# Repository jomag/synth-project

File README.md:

Project files for an experimental, DIY modular synth in Eurorack format.

## Casing

Threaded strips: 2x5x432 mm (also available in 203.2 mm). Hole distance: 5.08 mm.

https://gie-tec.de/product/threaded-strips/?lang=en

## References

A lot of generic and module specific design tips:
http://dintree.com/

Precision tuning of the AS3340 VCO
https://cabintechglobal.com/tune3340
http://www.alfarzpp.lv/eng/sc/Tuning%20the%20AS3340.pdf

CEM3340 VCO (Voltage Controlled Oscillator) designs
https://electricdruid.net/cem3340-vco-voltage-controlled-oscillator-designs/

Kassutronics blog: VCO CEM3340:
https://kassu2000.blogspot.com/2018/06/vco-3340.html

Collection of a few simple Eurorack module PCB and some notes about
components etc:
https://github.com/nickajeglin/Eurorack-pcbs

Understanding audio jack switches
https://www.cuidevices.com/blog/understanding-audio-jack-switches-and-schematic

Timo Rozendal CEM3340 VCO design
http://www.timorozendal.com/files/cem3340vco_schematic.pdfs

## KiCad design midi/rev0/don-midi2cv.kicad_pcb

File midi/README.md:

# MIDI to CV interface

## Dev environment

### Build Toolchain

The [GNU Arm Embedded Toolchain](https://developer.arm.com/tools-and-software/open-source-software/developer-tools/gnu-toolchain/gnu-rm/downloads) is used to build the firmware. This toolchain contains C compiler, assembler and linker for the 32-bit Arm Cortex-A, Cortex-M and
Cortex-R CPU families.

There are many ways to install the toochain on both MacOS
and Linux. This project assumes that the tarball has been
downloaded [from here](https://developer.arm.com/tools-and-software/open-source-software/developer-tools/gnu-toolchain/gnu-rm/downloads), extracted, and that the `bin`
directory has been added to `$PATH`.

Current version as of this writing is: 9-2020-q2-update,
released June 30, 2020.

**Note for MacOS:** From Catalina, the binaries will not
be able to start, as they are not verified. Use this command
to fix it:

```sh
$ xattr -d com.apple.quarantine `which arm-none-eabi-gcc`
```

### Rust

Make sure you have Rust and Cargo installed with `rustup`.
Current version of `rustc` as of this writing is _1.47.0_.

Add support for Arm Cortex-M3 as target:

```sh
$ rustup target add thumbv7m-none-eabi
```

### OpenOCD

OpenOCD is used to transfer firmware to the device. On
MacOS it is easiest installed using homebrew:

```sh
$ brew install openocd
```

Current version as of this writing: _0.10.0_

### cargo-binutils

_Not sure what these tools do yet, as I'm still learning
embedded Rust!_

```sh
$ cargo install cargo-binutils
$ rustup component add llvm-tools
```

### cargo-generate

_Used to start a Rust project based on a template. Not
required for building the firmware._

```sh
$ cargo install cargo-generate
```

## References

- [The Embedded Rust Book](https://rust-embedded.github.io/book/)
- Blog post: [STM32L0 Rust Part 1 - Getting Started](https://craigjb.com/2019/12/31/stm32l0-rust/) by Craig J Bishop

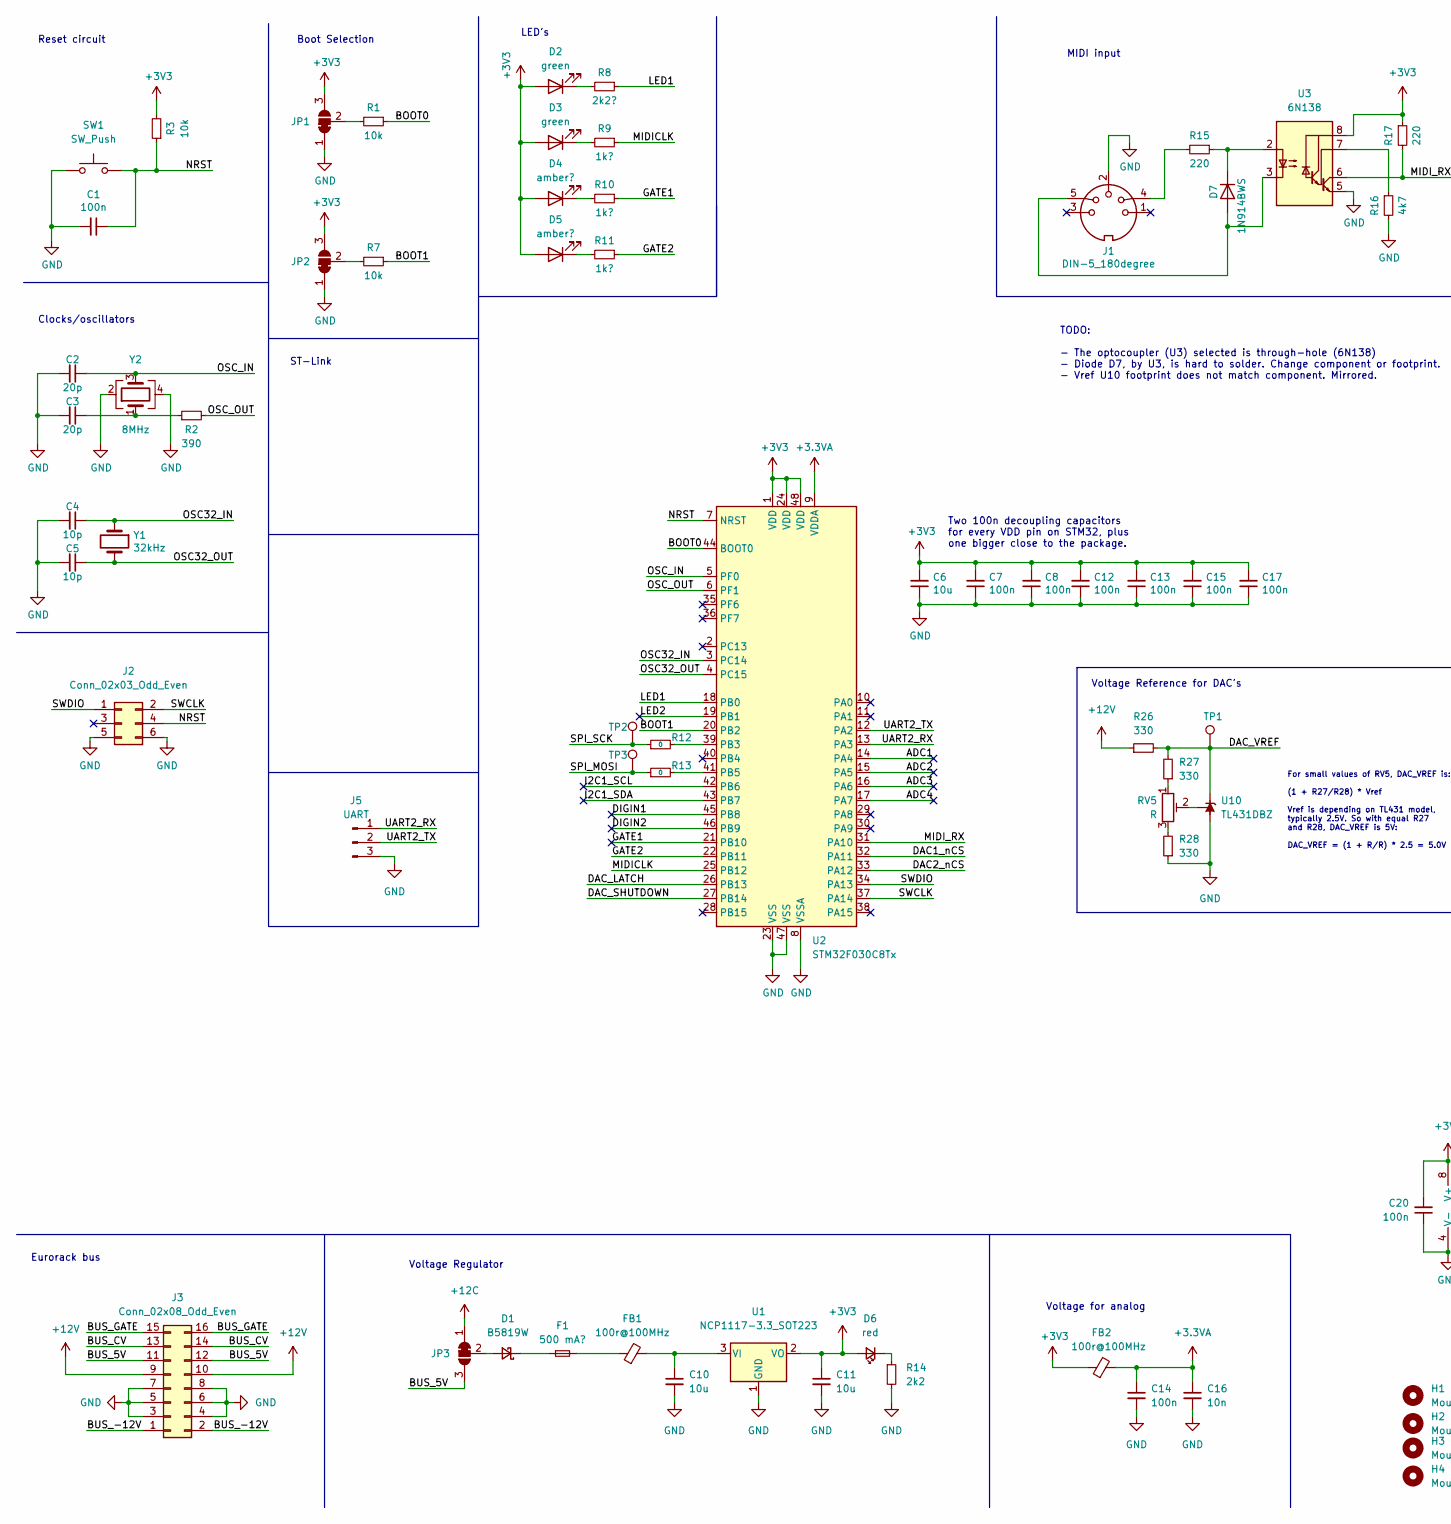
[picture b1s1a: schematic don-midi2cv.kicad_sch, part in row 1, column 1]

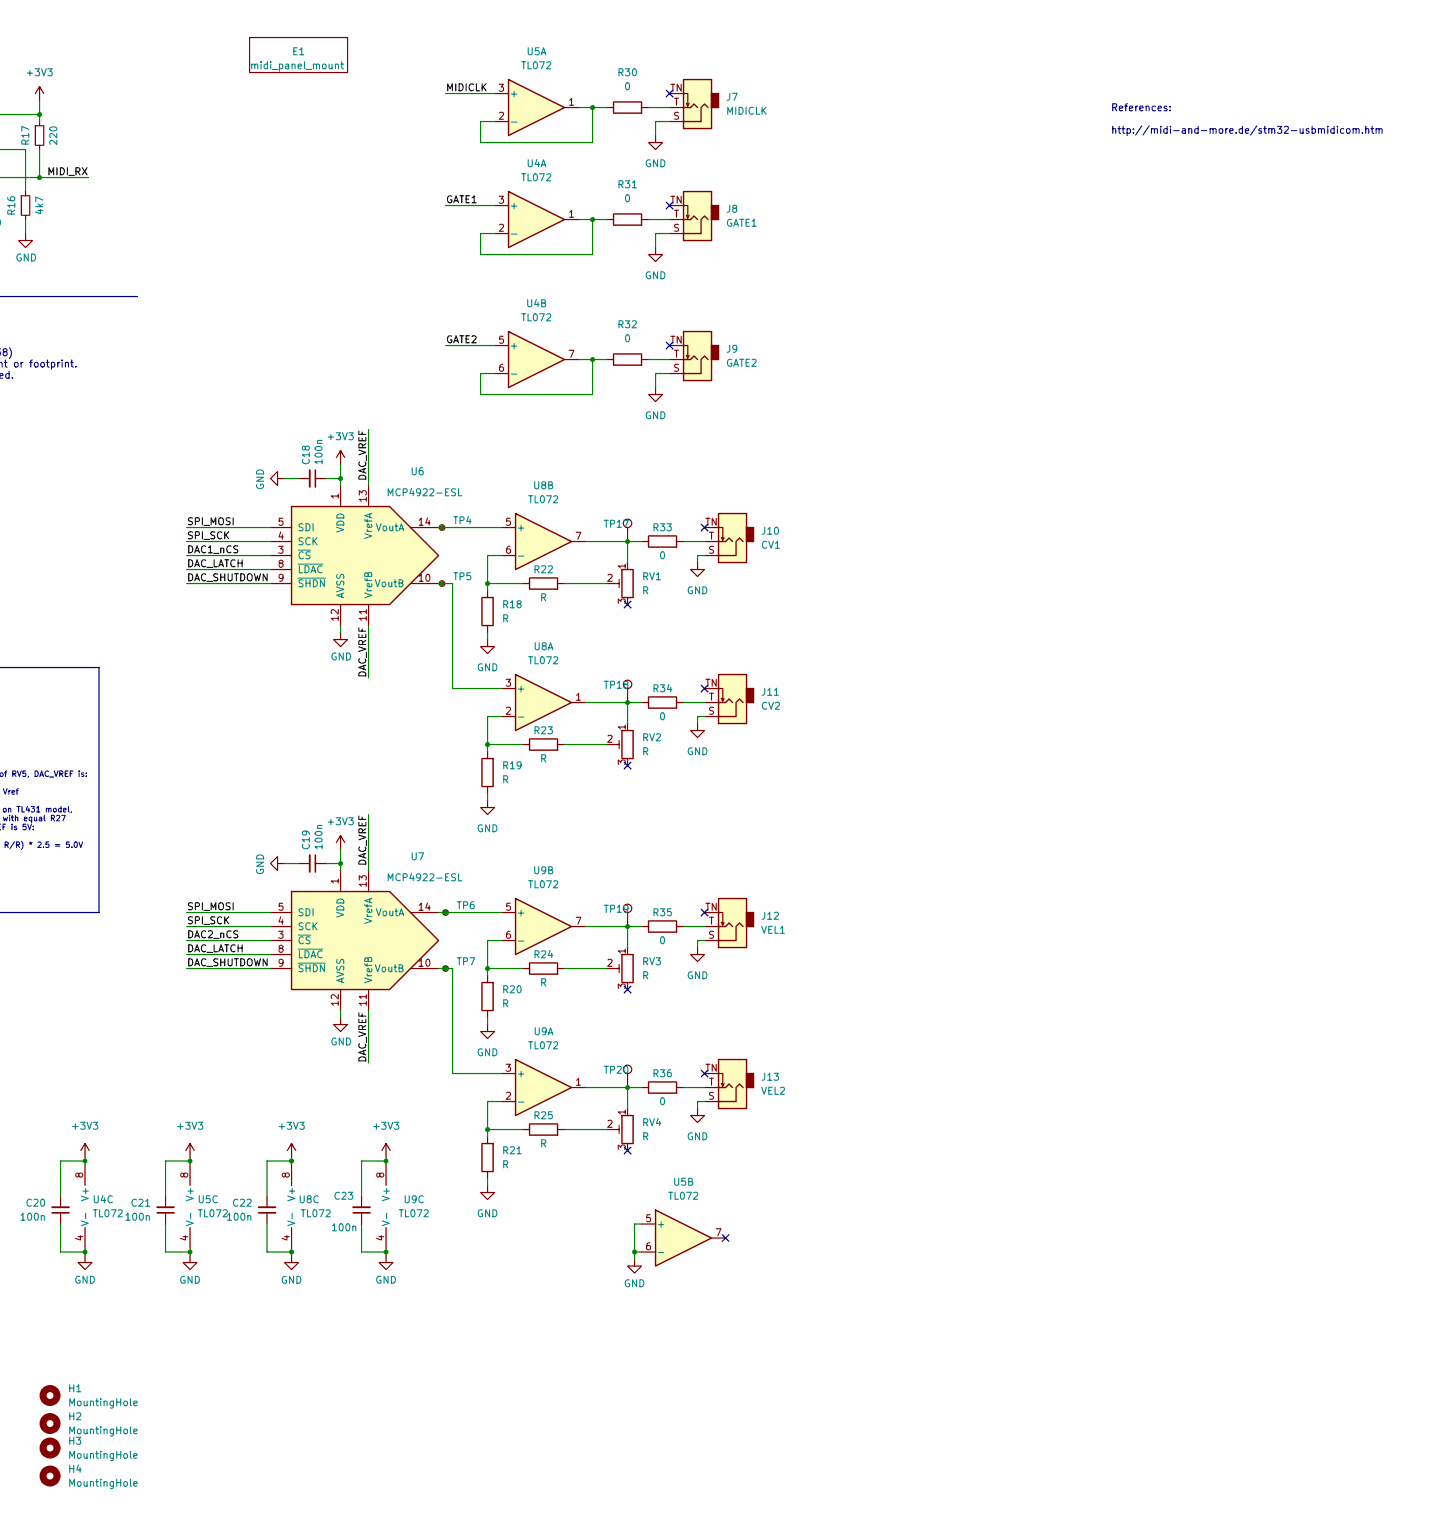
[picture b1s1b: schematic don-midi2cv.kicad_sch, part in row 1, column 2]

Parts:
C1, C7, C8, C12, C13, C14, C15, C17, C18, C19, C20, C21, C22, C23: 100n; C_0603_1608Metric; PartID CAP0015
C2, C3: 20p; C_0603_1608Metric; LCSC CC0603JRNPO9BN200
C4, C5: 10p; C_0603_1608Metric; LCSC CC0603JRNPO9BN100
C6, C10, C11: 10u; C_0805_2012Metric; PartID CAP0020
C16: 10n; C_0603_1608Metric; PartID CAP0038
D1: B5819W; D_SOD-123; LCSC C2910056
D2, D3: green; LED_0603_1608Metric; LCSC C434423
D4, D5: amber?; LED_0603_1608Metric; LCSC C434425
D6: red; LED_0603_1608Metric; LCSC C434419
D7: 1N914BWS; D_SOD-323F; Digikey 1N914BWSCT-ND
E1: midi_panel_mount; DIN Panel Mount Electrokit
F1: 500 mA?; Fuse_0603_1608Metric; LCSC C310922
FB1, FB2: 100r@100MHz; L_0805_2012Metric; PartID skip for now?
H1, H2, H3, H4: MountingHole; MountingHole_3.2mm_M3
J1: DIN-5_180degree; PinHeader_1x05_P2.54mm_Vertical
J2: Conn_02x03_Odd_Even; PinHeader_2x03_P2.54mm_Vertical; PartID stock; Digikey stock
J3: Conn_02x08_Odd_Even; PinHeader_2x08_P2.54mm_Vertical; PartID stock; Digikey stock
J5: UART; PinHeader_1x03_P2.54mm_Vertical; PartID stock; Digikey stock
J7: MIDICLK; Jack_3.5mm_QingPu_WQP-PJ398SM_Vertical_CircularHoles
J8: GATE1; Jack_3.5mm_QingPu_WQP-PJ398SM_Vertical_CircularHoles
J9: GATE2; Jack_3.5mm_QingPu_WQP-PJ398SM_Vertical_CircularHoles
J10: CV1; Jack_3.5mm_QingPu_WQP-PJ398SM_Vertical_CircularHoles
J11: CV2; Jack_3.5mm_QingPu_WQP-PJ398SM_Vertical_CircularHoles
J12: VEL1; Jack_3.5mm_QingPu_WQP-PJ398SM_Vertical_CircularHoles
J13: VEL2; Jack_3.5mm_QingPu_WQP-PJ398SM_Vertical_CircularHoles
JP1, JP2, JP3: SolderJumper_3_Bridged12; SolderJumper-3_P1.3mm_Bridged12_Pad1.0x1.5mm
R1, R3, R7: 10k; R_0603_1608Metric; PartID RES0011
R2: 390; R_0603_1608Metric; LCSC C114620
R8: 2k2?; R_0603_1608Metric; PartID RES0038; LCSC C114662
R9, R10, R11: 1k?; R_0603_1608Metric; PartID RES0013
R12, R13, R30, R31, R32, R33, R34, R35, R36: 0; R_0603_1608Metric; PartID RES0027
R14: 2k2; R_0603_1608Metric; PartID RES0038; LCSC C114662
R15, R17: 220; R_0603_1608Metric; LCSC C107696
R16: 4k7; R_0603_1608Metric; PartID RES0010
R18, R19, R20, R21, R22, R23, R24, R25: R; R_0603_1608Metric
R26, R27, R28: 330; R_0603_1608Metric; LCSC C105881
RV1, RV2, RV3, RV4, RV5: R; Potentiometer_Bourns_TC33X_Vertical; PartID POT002?; LCSC C720647 / C720646 / C719174 / C720648 /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
SW1: SW_Push; SW_PUSH_6mm; LCSC C393938
TP1, TP2, TP3, TP17, TP18, TP19, TP20: TestPoint; TestPoint_Pad_D1.5mm
TP4, TP5, TP6, TP7: TestPoint_Small; TestPoint_Pad_D1.5mm
U1: NCP1117-3.3_SOT223; SOT-223-3_TabPin2; LCSC C146799 (or C26537)
U2: STM32F030C8Tx; LQFP-48_7x7mm_P0.5mm; LCSC C23922
U3: 6N138; SOP-8_6.62x9.15mm_P2.54mm; LCSC C188666 or C3001991
U4, U5, U8, U9: TL072; SOIC-8_3.9x4.9mm_P1.27mm; LCSC C6962
U6, U7: MCP4922-ESL; SOIC-14_3.9x8.7mm_P1.27mm; LCSC C39851
U10: TL431DBZ; SOT-23; LCSC C713689
Y1: 32kHz; Crystal_SMD_3215-2Pin_3.2x1.5mm; LCSC C655072
Y2: 8MHz; Crystal_SMD_3225-4Pin_3.2x2.5mm_HandSoldering; LCSC C648985

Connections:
+3.3VA: C14.1, C16.1, FB2.2, U2.9 (VDDA)
+3V3: C6.2, C7.2, C8.2, C11.1, C12.2, C13.2, C15.2, C17.2, C18.1, C19.1, C20.2, C21.2, C22.2, C23.2, D2.2 (A), D3.2 (A), D4.2 (A), D5.2 (A), D6.2 (A), FB2.1, JP1.3 (B), JP2.3 (B), R3.2, R17.1, U1.2 (VO), U2.1 (VDD), U2.24 (VDD), U2.48 (VDD), U3.8 (VCC), U4.8 (V+), U5.8 (V+), U6.1 (VDD), U7.1 (VDD), U8.8 (V+), U9.8 (V+)
+12C: JP3.1 (A)
+12V: J3.9, J3.10, R26.1
/ADC1: U2.14 (PA4)
/ADC2: U2.15 (PA5)
/ADC3: U2.16 (PA6)
/ADC4: U2.17 (PA7)
/BOOT0: R1.1, U2.44 (BOOT0)
/BOOT1: R7.1, U2.20 (PB2)
/BUS_5V: J3.11, J3.12, JP3.3 (B)
/BUS_-12V: J3.1, J3.2
/BUS_CV: J3.13, J3.14
/BUS_GATE: J3.15, J3.16
/DAC1_nCS: U2.32 (PA11), U6.3 (~CS)
/DAC2_nCS: U2.33 (PA12), U7.3 (~CS)
/DAC_LATCH: U2.26 (PB13), U6.8 (~LDAC), U7.8 (~LDAC)
/DAC_SHUTDOWN: U2.27 (PB14), U6.9 (~SHDN), U7.9 (~SHDN)
/DAC_VREF: R26.2, R27.2, TP1.1, U6.11 (VrefB), U6.13 (VrefA), U7.11 (VrefB), U7.13 (VrefA), U10.1 (K)
/DIGIN1: U2.45 (PB8)
/DIGIN2: U2.46 (PB9)
/GATE1: R10.1, U2.21 (PB10), U4.3 (+)
/GATE2: R11.1, U2.22 (PB11), U4.5 (+)
/I2C1_SCL: U2.42 (PB6)
/I2C1_SDA: U2.43 (PB7)
/LED1: R8.1, U2.18 (PB0)
/LED2: U2.19 (PB1)
/MIDICLK: R9.1, U2.25 (PB12), U5.3 (+)
/MIDI_RX: R17.2, U2.31 (PA10), U3.6 (VO2)
/NRST: C1.1, J2.4, R3.1, SW1.2, U2.7 (NRST)
/OSC32_IN: C4.1, U2.3 (PC14), Y1.1
/OSC32_OUT: C5.1, U2.4 (PC15), Y1.2
/OSC_IN: C2.1, U2.5 (PF0), Y2.3
/OSC_OUT: R2.2, U2.6 (PF1)
/SPI_MOSI: R13.1, TP3.1, U6.5 (SDI), U7.5 (SDI)
/SPI_SCK: R12.1, TP2.1, U6.4 (SCK), U7.4 (SCK)
/SWCLK: J2.2, U2.37 (PA14)
/SWDIO: J2.1, U2.34 (PA13)
/UART2_RX: J5.1, U2.13 (PA3)
/UART2_TX: J5.2, U2.12 (PA2)
GND: C1.2, C2.2, C3.2, C4.2, C5.2, C6.1, C7.1, C8.1, C10.2, C11.2, C12.1, C13.1, C14.2, C15.1, C16.2, C17.1, C18.2, C19.2, C20.1, C21.1, C22.1, C23.1, J1.2, J2.5, J2.6, J3.3, J3.4, J3.5, J3.6, J3.7, J3.8, J5.3, J7.S, J8.S, J9.S, J10.S, J11.S, J12.S, J13.S, JP1.1 (A), JP2.1 (A), R14.2, R16.2, R18.1, R19.1, R20.1, R21.1, R28.1, SW1.1, U1.1 (GND), U2.8 (VSSA), U2.23 (VSS), U2.47 (VSS), U3.5 (GND), U4.4 (V-), U5.4 (V-), U5.5 (+), U5.6 (-), U6.12 (AVSS), U7.12 (AVSS), U8.4 (V-), U9.4 (V-), U10.3 (A), Y2.2, Y2.4
unnamed: C3.1, R2.1, Y2.1
unnamed: D1.2 (A), JP3.2 (C)
unnamed: D1.1 (K), F1.1
unnamed: D2.1 (K), R8.2
unnamed: D3.1 (K), R9.2
unnamed: D4.1 (K), R10.2
unnamed: D5.1 (K), R11.2
unnamed: D6.1 (K), R14.1
unnamed: D7.2 (A), J1.5, U3.3 (C2)
unnamed: D7.1 (K), R15.1, U3.2 (C1)
unnamed: F1.2, FB1.1
unnamed: J1.4, R15.2
unnamed: J7.T, R30.2
unnamed: J8.T, R31.2
unnamed: J9.T, R32.2
unnamed: J10.T, R33.2
unnamed: J11.T, R34.2
unnamed: J12.T, R35.2
unnamed: J13.T, R36.2
unnamed: JP1.2 (C), R1.2
unnamed: JP2.2 (C), R7.2
unnamed: R22.2, RV1.2
unnamed: R23.2, RV2.2
unnamed: R24.2, RV3.2
unnamed: R25.2, RV4.2
unnamed: R27.1, RV5.1
unnamed: R28.2, RV5.3
unnamed: R33.1, RV1.1, TP17.1, U8.7
unnamed: R34.1, RV2.1, TP18.1, U8.1
unnamed: R35.1, RV3.1, TP19.1, U9.7
unnamed: R36.1, RV4.1, TP20.1, U9.1
unnamed: C10.1, FB1.2, U1.3 (VI)
unnamed: R12.2, U2.39 (PB3)
unnamed: R13.2, U2.41 (PB5)
unnamed: R16.1, U3.7 (VO1)
unnamed: R31.1, U4.1, U4.2 (-)
unnamed: R32.1, U4.6 (-), U4.7
unnamed: R30.1, U5.1, U5.2 (-)
unnamed: TP4.1, U6.14 (VoutA), U8.5 (+)
unnamed: TP5.1, U6.10 (VoutB), U8.3 (+)
unnamed: TP6.1, U7.14 (VoutA), U9.5 (+)
unnamed: TP7.1, U7.10 (VoutB), U9.3 (+)
unnamed: R19.2, R23.1, U8.2 (-)
unnamed: R18.2, R22.1, U8.6 (-)
unnamed: R21.2, R25.1, U9.2 (-)
unnamed: R20.2, R24.1, U9.6 (-)
unnamed: RV5.2, U10.2 (REF)

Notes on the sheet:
ST-Link
Voltage Regulator
Eurorack bus
References: http://midi-and-more.de/stm32-usbmidicom.htm
MIDI input
Reset circuit
Voltage Reference for DAC's
LED's
Boot Selection
Clocks/oscillators
Two 100n decoupling capacitors for every VDD pin on STM32, plus one bigger close to the package.
For small values of RV5, DAC_VREF is: (1 + R27/R28) * Vref Vref is depending on TL431 model, typically 2.5V. So with equal R27 and R28, DAC_VREF is 5V: DAC_VREF = (1 + R/R) * 2.5 = 5.0V
Voltage for analog
TODO: - The optocoupler (U3) selected is through-hole (6N138) - Diode D7, by U3, is hard to solder. Change component or footprint. - Vref U10 footprint does not match component. Mirrored.

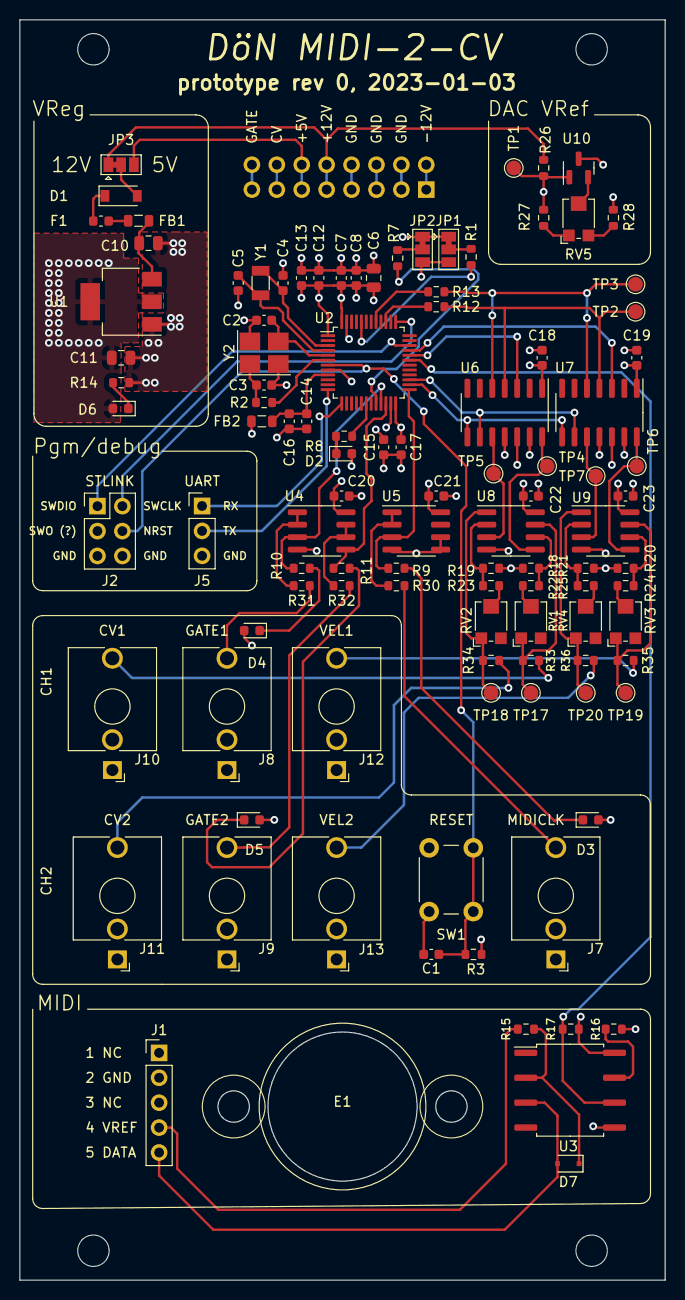
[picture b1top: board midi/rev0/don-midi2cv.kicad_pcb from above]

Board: 4 copper layers, 65.7 x 128.4 mm, 112 parts (1 on the bottom side), 78 nets.

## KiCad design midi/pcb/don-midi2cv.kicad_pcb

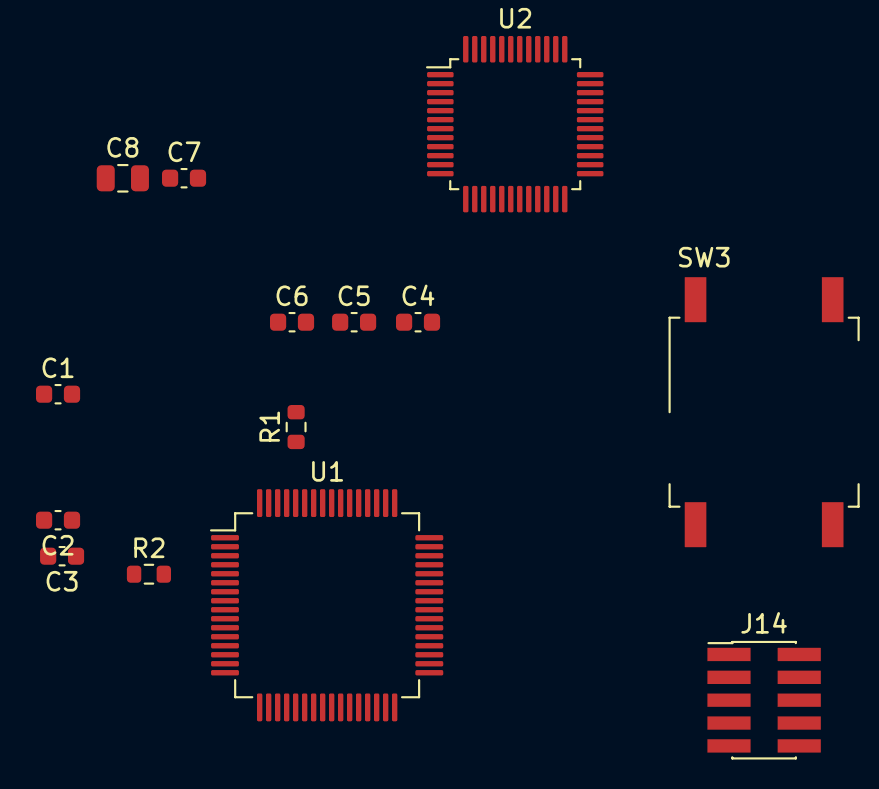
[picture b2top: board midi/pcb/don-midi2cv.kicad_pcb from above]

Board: 2 copper layers, 14 parts (0 on the bottom side), 11 nets, no tracks yet.

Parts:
C1, C6, C7: 100n; C_0603_1608Metric
C2, C3: 20p?; C_0603_1608Metric
C4: 1u; C_0603_1608Metric
C5: 10n; C_0603_1608Metric
C8: 4.7u; C_0805_2012Metric
J14: Conn_02x05_Odd_Even; PinHeader_2x05_P1.27mm_Vertical_SMD
R1: R_Small; R_0603_1608Metric
R2: 390?; R_0603_1608Metric
SW3: SW_MEC_5E; SW_MEC_5GSH9
U1: STM32F030R8Tx; LQFP-64_10x10mm_P0.5mm
U2: STM32F070CBTx; LQFP-48_7x7mm_P0.5mm

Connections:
+3V3: C6.2, C7.2, C8.2, J14.1, U1.1, U1.32, U1.64
/NRST: C1.1, J14.10, SW3.3, SW3.4, U1.7
/SWCLK: J14.4, U1.49
/SWDIO: J14.2, U1.46
GND: C1.2, C2.2, C3.2, C6.1, C7.1, C8.1, J14.3, J14.5, J14.9, R1.2, SW3.1, SW3.2, U1.31, U1.63
GNDA: C4.1, C5.1, U1.12
unnamed: C2.1, U1.5
unnamed: C3.1, R2.1
unnamed: R1.1, U1.60
unnamed: R2.2, U1.6
VDDA: C4.2, C5.2, U1.13

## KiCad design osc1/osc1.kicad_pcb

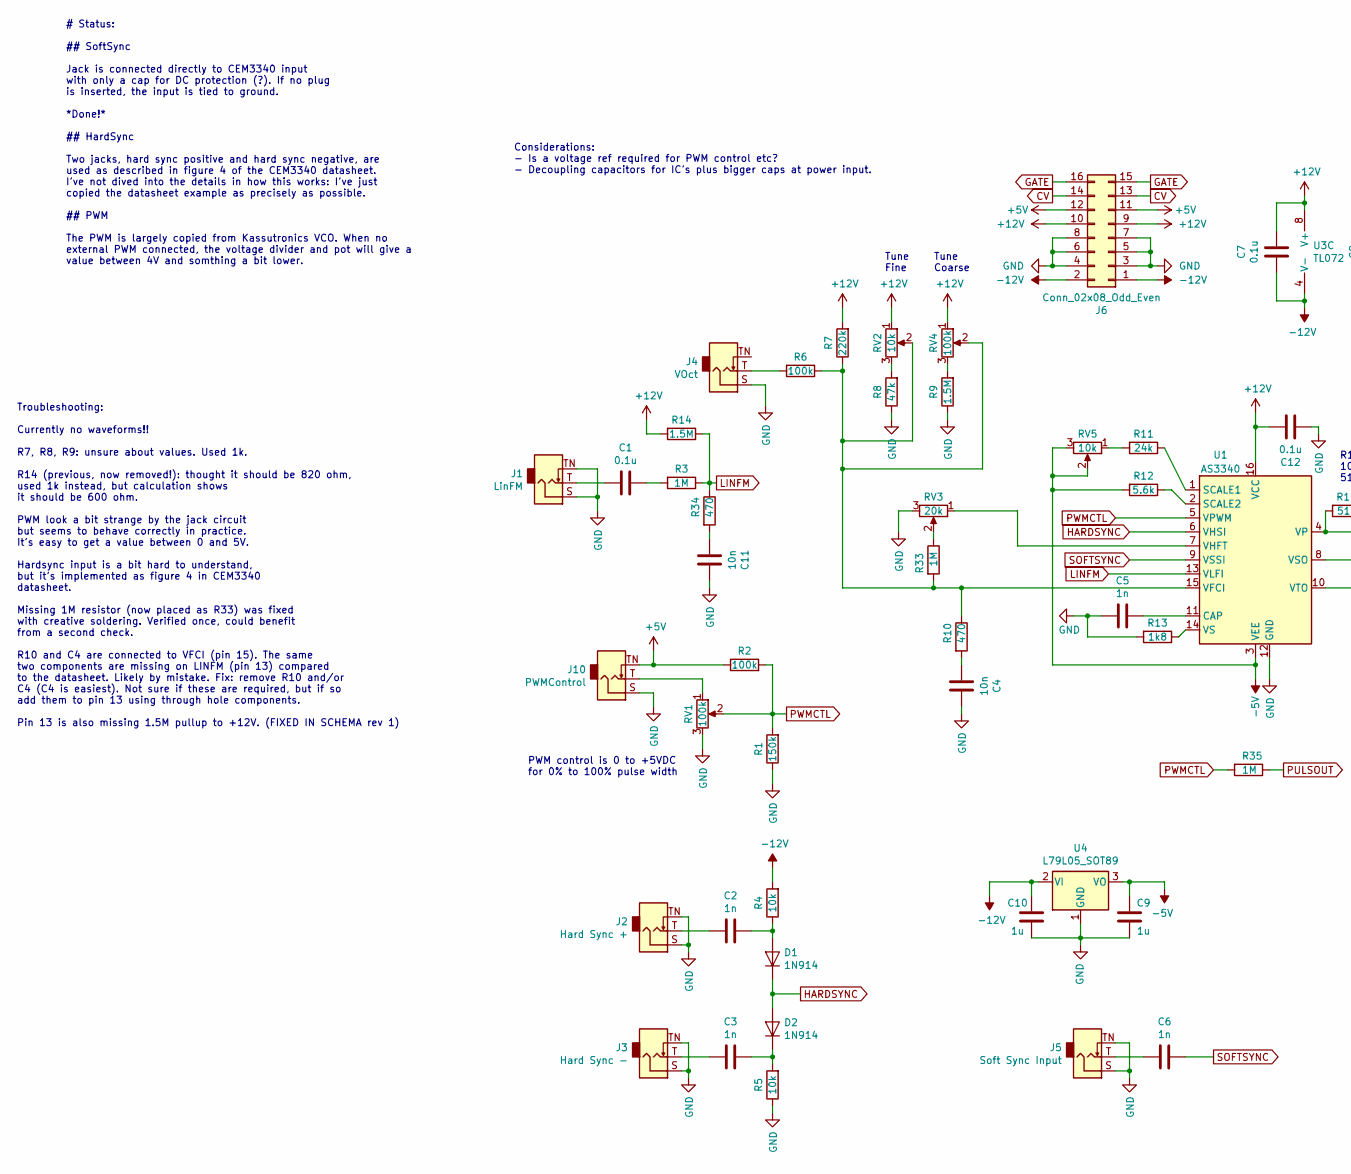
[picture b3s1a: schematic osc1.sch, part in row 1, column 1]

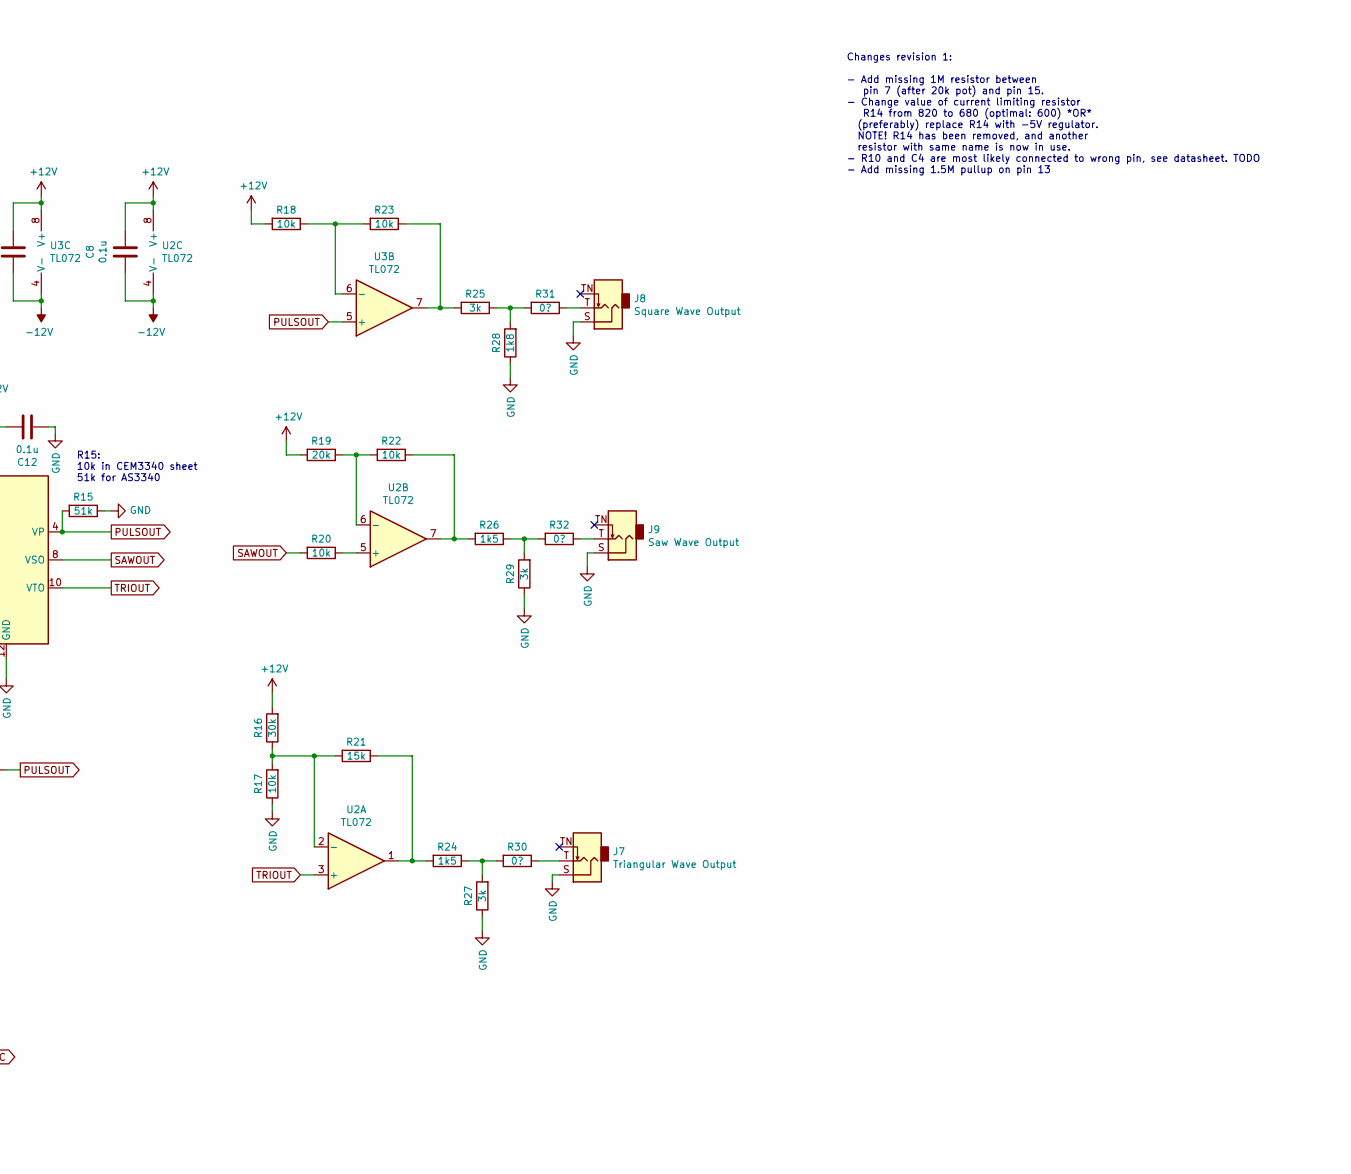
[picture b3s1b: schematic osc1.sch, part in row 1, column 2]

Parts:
C1, C7, C8, C12: 0.1u; C_0603_1608Metric
C2, C3, C5, C6: 1n; C_0603_1608Metric
C4, C11: 10n; C_0603_1608Metric
C9, C10: 1u; C_0603_1608Metric
D1, D2: 1N914; D_SOD-523
J1: LinFM; Jack_3.5mm_QingPu_WQP-PJ398SM_Vertical_CircularHoles
J2: Hard Sync +; Jack_3.5mm_QingPu_WQP-PJ398SM_Vertical_CircularHoles
J3: Hard Sync -; Jack_3.5mm_QingPu_WQP-PJ398SM_Vertical_CircularHoles
J4: VOct; Jack_3.5mm_QingPu_WQP-PJ398SM_Vertical_CircularHoles
J5: Soft Sync Input; Jack_3.5mm_QingPu_WQP-PJ398SM_Vertical_CircularHoles
J6: Conn_02x08_Odd_Even; IDC-Header_2x08_P2.54mm_Vertical
J7: Triangular Wave Output; Jack_3.5mm_QingPu_WQP-PJ398SM_Vertical_CircularHoles
J8: Square Wave Output; Jack_3.5mm_QingPu_WQP-PJ398SM_Vertical_CircularHoles
J9: Saw Wave Output; Jack_3.5mm_QingPu_WQP-PJ398SM_Vertical_CircularHoles
J10: PWMControl; Jack_3.5mm_QingPu_WQP-PJ398SM_Vertical_CircularHoles
R1: 150k; R_0603_1608Metric
R2, R6: 100k; R_0603_1608Metric
R3, R33, R35: 1M; R_0603_1608Metric
R4, R5, R17, R18, R20, R22, R23: 10k; R_0603_1608Metric
R7: 220k; R_0603_1608Metric
R8: 47k; R_0603_1608Metric
R9, R14: 1.5M; R_0603_1608Metric
R10, R34: 470; R_0603_1608Metric
R11: 24k; R_0603_1608Metric
R12: 5.6k; R_0603_1608Metric
R13, R28: 1k8; R_0603_1608Metric
R15: 51k; R_0603_1608Metric
R16: 30k; R_0603_1608Metric
R19: 20k; R_0603_1608Metric
R21: 15k; R_0603_1608Metric
R24, R26: 1k5; R_0603_1608Metric
R25, R27, R29: 3k; R_0603_1608Metric
R30, R31, R32: 0?; R_0603_1608Metric
RV1, RV4: 100k; Potentiometer_Alpha_RD901F-40-00D_Single_Vertical_CircularH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
RV2: 10k; Potentiometer_Alpha_RD901F-40-00D_Single_Vertical_CircularH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
RV3: 20k; Potentiometer_Bourns_3296W_Vertical
RV5: 10k; Potentiometer_Bourns_3296W_Vertical
U1: AS3340; DIP-16_W7.62mm_Socket
U2, U3: TL072; SO-8_3.9x4.9mm_P1.27mm
U4: L79L05_SOT89; SOT-89-3

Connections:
+5V: J6.11, J6.12, J10.TN, R2.1
+12V: C7.1, C8.1, C12.1, J6.9, J6.10, R7.2, R14.2, R16.2, R18.2, R19.2, RV2.1, RV4.1, U1.16 (VCC), U2.8 (V+), U3.8 (V+)
-5V: C9.1, R12.2, RV5.2, RV5.3, U1.3 (VEE), U4.3 (VO)
-12V: C7.2, C8.2, C10.2, J6.1, J6.2, R4.2, U2.4 (V-), U3.4 (V-), U4.2 (VI)
CV: J6.13, J6.14
GATE: J6.15, J6.16
GND: C4.1, C5.2, C9.2, C10.1, C11.1, C12.2, J1.S, J1.TN, J2.S, J2.TN, J3.S, J3.TN, J4.S, J5.S, J5.TN, J6.3, J6.4, J6.5, J6.6, J6.7, J6.8, J7.S, J8.S, J9.S, J10.S, R1.1, R5.1, R8.1, R9.1, R13.2, R15.1, R17.1, R27.1, R28.1, R29.1, RV1.3, RV3.3, U1.12 (GND), U4.1 (GND)
HARDSYNC: D1.1 (K), D2.2 (A), U1.6 (VHSI)
LINFM: R3.1, R14.1, R34.1, U1.13 (VLFI)
unnamed: C1.1, R3.2
unnamed: C1.2, J1.T
unnamed: C2.1, D1.2 (A), R4.1
unnamed: C2.2, J2.T
unnamed: C3.1, D2.1 (K), R5.2
unnamed: C3.2, J3.T
unnamed: C4.2, R10.2
unnamed: C5.1, U1.11 (CAP)
unnamed: C6.2, J5.T
unnamed: C11.2, R34.2
unnamed: J4.T, R6.2
unnamed: J7.T, R30.1
unnamed: J8.T, R31.1
unnamed: J9.T, R32.1
unnamed: J10.T, RV1.1
unnamed: R8.2, RV2.3
unnamed: R9.2, RV4.3
unnamed: R6.1, R7.1, R10.1, R33.2, RV2.2, RV4.2, U1.15 (VFCI)
unnamed: R11.1, U1.1 (SCALE1)
unnamed: R11.2, RV5.1
unnamed: R12.1, U1.2 (SCALE2)
unnamed: R13.1, U1.14 (VS)
unnamed: R16.1, R17.2, R21.2, U2.2 (-)
unnamed: R18.1, R23.2, U3.6 (-)
unnamed: R19.1, R22.2, U2.6 (-)
unnamed: R20.1, U2.5 (+)
unnamed: R21.1, R24.2, U2.1
unnamed: R22.1, R26.2, U2.7
unnamed: R23.1, R25.2, U3.7
unnamed: R24.1, R27.2, R30.2
unnamed: R25.1, R28.2, R31.2
unnamed: R26.1, R29.2, R32.2
unnamed: R33.1, RV3.2
unnamed: RV3.1, U1.7 (VHFT)
PULSOUT: R15.2, R35.1, U1.4 (VP), U3.5 (+)
PWMCTL: R1.2, R2.2, R35.2, RV1.2, U1.5 (VPWM)
SAWOUT: R20.2, U1.8 (VSO)
SOFTSYNC: C6.1, U1.9 (VSSI)
TRIOUT: U1.10 (VTO), U2.3 (+)

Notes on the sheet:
PWM control is 0 to +5VDC for 0% to 100% pulse width
Considerations: - Is a voltage ref required for PWM control etc? - Decoupling capacitors for IC’s plus bigger caps at power input.
# Status: ## SoftSync Jack is connected directly to CEM3340 input with only a cap for DC protection (?). If no plug is inserted, the input is tied to ground. *Done!* ## HardSync Two jacks, hard sync positive and hard sync negative, are used as described in figure 4 of the CEM3340 datasheet. I’ve no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
Troubleshooting: Currently no waveforms!! R7, R8, R9: unsure about values. Used 1k. R14 (previous, now removed!): thought it should be 820 ohm, used 1k instead, but calculation shows it should be 600 ohm. PWM look a bit strange by the jack circuit but seems to behave correctly in practice. It’s eas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
R15: 10k in CEM3340 sheet 51k for AS3340
Changes revision 1: - Add missing 1M resistor between pin 7 (after 20k pot) and pin 15. - Change value of current limiting resistor R14 from 820 to 680 (optimal: 600) *OR* (preferably) replace R14 with -5V regulator. NOTE! R14 has been removed, and another resistor with same name is now in use. - R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
Tune Fine
Tune Coarse

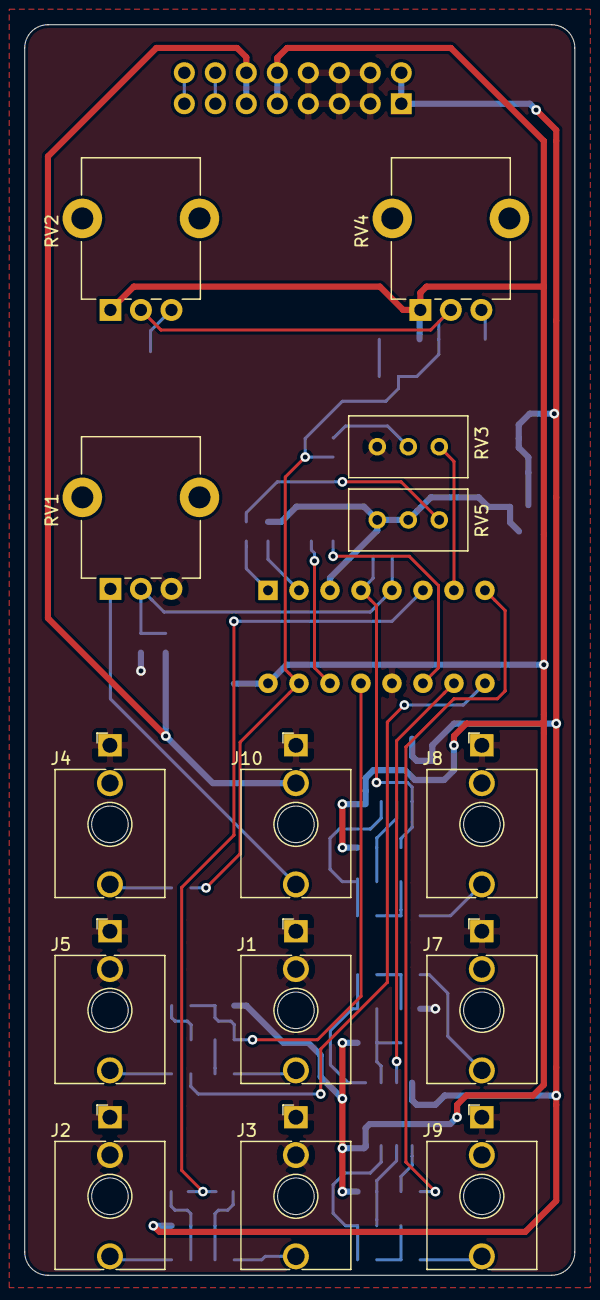
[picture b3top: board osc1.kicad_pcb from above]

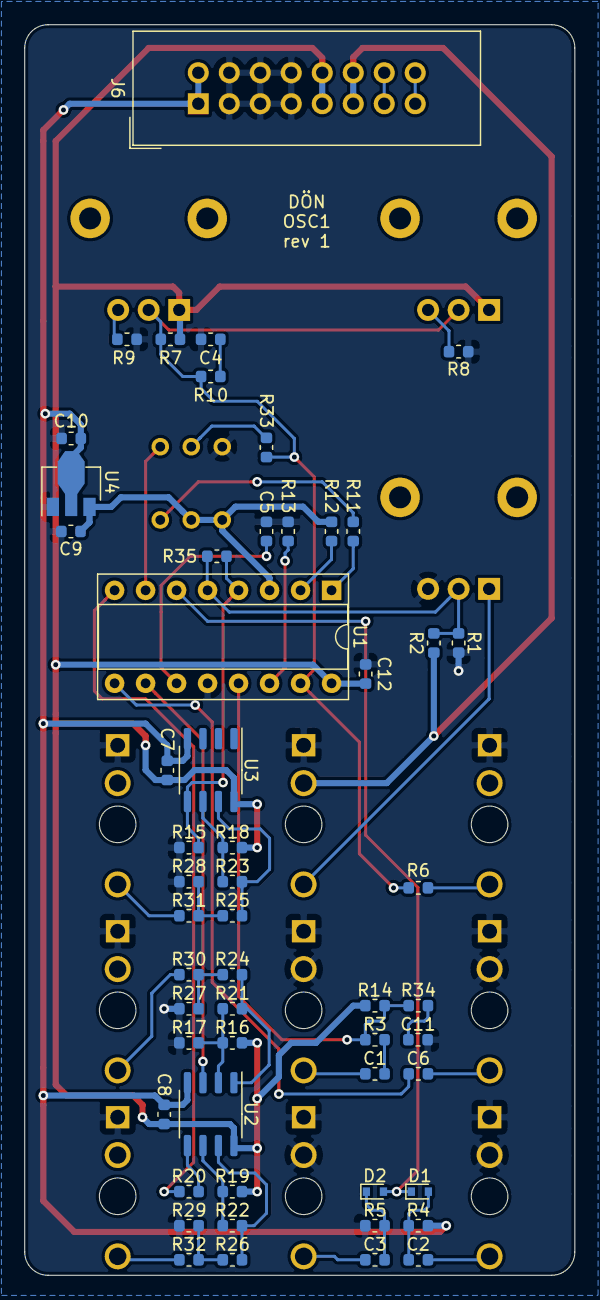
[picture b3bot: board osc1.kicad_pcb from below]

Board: 2 copper layers, 45.1 x 102.5 mm, 68 parts (54 on the bottom side), 48 nets.

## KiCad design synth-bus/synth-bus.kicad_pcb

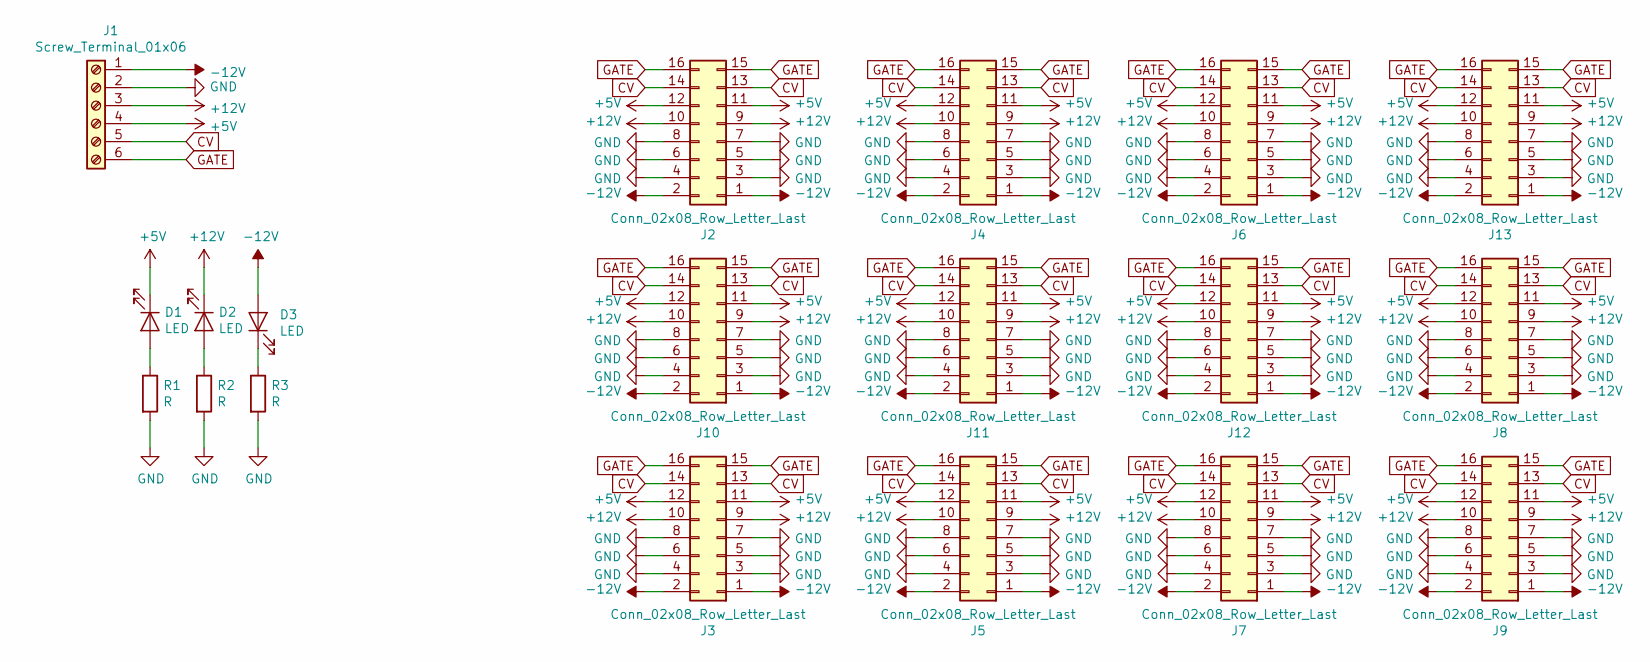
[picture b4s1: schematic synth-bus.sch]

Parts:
D1, D2, D3: LED; LED_0805_2012Metric_Pad1.15x1.40mm_HandSolder
J1: Screw_Terminal_01x06; TerminalBlock_Phoenix_MKDS-3-6-5.08_1x06_P5.08mm_Horizontal
J2, J3, J4, J5, J6, J7, J8, J9, J10, J11, J12, J13: Conn_02x08_Row_Letter_Last; Multicomp_MC9A12-1634_2x08_P2.54mm_Vertical
R1, R2, R3: R; R_0603_1608Metric_Pad1.05x0.95mm_HandSolder

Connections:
+5V: D1.1 (K), J1.4, J2.11, J2.12, J3.11, J3.12, J4.11, J4.12, J5.11, J5.12, J6.11, J6.12, J7.11, J7.12, J8.11, J8.12, J9.11, J9.12, J10.11, J10.12, J11.11, J11.12, J12.11, J12.12, J13.11, J13.12
+12V: D2.1 (K), J1.3, J2.9, J2.10, J3.9, J3.10, J4.9, J4.10, J5.9, J5.10, J6.9, J6.10, J7.9, J7.10, J8.9, J8.10, J9.9, J9.10, J10.9, J10.10, J11.9, J11.10, J12.9, J12.10, J13.9, J13.10
-12V: D3.2 (A), J1.1, J2.1, J2.2, J3.1, J3.2, J4.1, J4.2, J5.1, J5.2, J6.1, J6.2, J7.1, J7.2, J8.1, J8.2, J9.1, J9.2, J10.1, J10.2, J11.1, J11.2, J12.1, J12.2, J13.1, J13.2
CV: J1.5, J2.13, J2.14, J3.13, J3.14, J4.13, J4.14, J5.13, J5.14, J6.13, J6.14, J7.13, J7.14, J8.13, J8.14, J9.13, J9.14, J10.13, J10.14, J11.13, J11.14, J12.13, J12.14, J13.13, J13.14
GATE: J1.6, J2.15, J2.16, J3.15, J3.16, J4.15, J4.16, J5.15, J5.16, J6.15, J6.16, J7.15, J7.16, J8.15, J8.16, J9.15, J9.16, J10.15, J10.16, J11.15, J11.16, J12.15, J12.16, J13.15, J13.16
GND: J1.2, J2.3, J2.4, J2.5, J2.6, J2.7, J2.8, J3.3, J3.4, J3.5, J3.6, J3.7, J3.8, J4.3, J4.4, J4.5, J4.6, J4.7, J4.8, J5.3, J5.4, J5.5, J5.6, J5.7, J5.8, J6.3, J6.4, J6.5, J6.6, J6.7, J6.8, J7.3, J7.4, J7.5, J7.6, J7.7, J7.8, J8.3, J8.4, J8.5, J8.6, J8.7, J8.8, J9.3, J9.4, J9.5, J9.6, J9.7, J9.8, J10.3, J10.4, J10.5, J10.6, J10.7, J10.8, J11.3, J11.4, J11.5, J11.6, J11.7, J11.8, J12.3, J12.4, J12.5, J12.6, J12.7, J12.8, J13.3, J13.4, J13.5, J13.6, J13.7, J13.8, R1.2, R2.2, R3.2
unnamed: D1.2 (A), R1.1
unnamed: D2.2 (A), R2.1
unnamed: D3.1 (K), R3.1

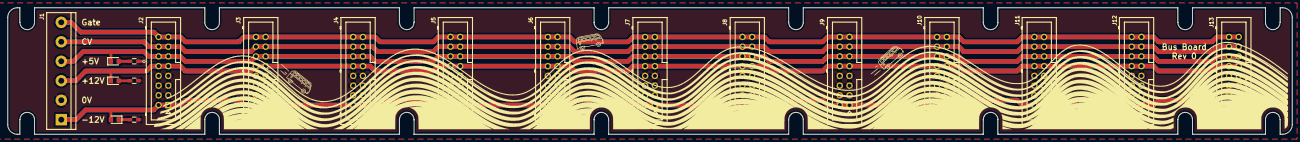
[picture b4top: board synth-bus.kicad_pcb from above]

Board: 2 copper layers, 335.3 x 33.0 mm, 20 parts (0 on the bottom side), 9 nets.

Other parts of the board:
Ref**: Val**; SynthBusArt

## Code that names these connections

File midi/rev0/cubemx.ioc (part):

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Mcu.Name=STM32F030C8Tx
Mcu.Package=LQFP48
Mcu.UserName=STM32F030C8Tx
PA10.Mode=Asynchronous
PA10.Signal=USART1_RX
PA11.GPIOParameters=GPIO_Label
PA11.GPIO_Label=DAC1_nCS
PA11.Signal=GPIO_Output
PA12.GPIOParameters=GPIO_Label
PA12.GPIO_Label=DAC2_nCS
PA12.Signal=GPIO_Output
PA13.Mode=Serial_Wire
PA13.Signal=SYS_SWDIO
PA14.Mode=Serial_Wire
PA14.Signal=SYS_SWCLK
PA2.Mode=Asynchronous
PA2.Signal=USART2_TX
PA3.Mode=Asynchronous
PA3.Signal=USART2_RX
PA4.Mode=IN4
PA4.Signal=ADC_IN4
PA5.Mode=IN5
PA5.Signal=ADC_IN5
PA6.Mode=IN6
PA6.Signal=ADC_IN6
PA7.Mode=IN7
PA7.Signal=ADC_IN7
PA9.Mode=Asynchronous
PA9.Signal=USART1_TX
PB0.GPIOParameters=GPIO_Label
PB0.GPIO_Label=LED1
PB0.Signal=GPIO_Output
PB1.GPIOParameters=GPIO_Label
PB1.GPIO_Label=LED2
PB1.Signal=GPIO_Output
PB10.GPIOParameters=GPIO_Label
PB10.GPIO_Label=GATE1
PB10.Signal=GPIO_Output
PB11.GPIOParameters=GPIO_Label
PB11.GPIO_Label=GATE2
PB11.Signal=GPIO_Output
PB12.GPIOParameters=GPIO_Label
PB12.GPIO_Label=MIDICLK
PB12.Signal=GPIO_Output
PB13.GPIOParameters=GPIO_Label
PB13.GPIO_Label=DAC_LATCH
PB13.Signal=GPIO_Output
PB14.GPIOParameters=GPIO_Label
PB14.GPIO_Label=DAC_SHUTDOWN
PB14.Signal=GPIO_Output
PB3.Mode=TX_Only_Simplex_Unidirect_Master
PB3.Signal=SPI1_SCK
PB5.Mode=TX_Only_Simplex_Unidirect_Master
PB5.Signal=SPI1_MOSI
PB6.Mode=I2C
PB6.Signal=I2C1_SCL
PB7.Mode=I2C
PB7.Signal=I2C1_SDA
PB8.GPIOParameters=GPIO_Label
PB8.GPIO_Label=DIGIN1
PB8.Signal=GPIO_Input
PB9.GPIOParameters=GPIO_Label
PB9.GPIO_Label=DIGIN2
PB9.Signal=GPIO_Input
PC14-OSC32_IN.Mode=LSE-External-Oscillator
PC14-OSC32_IN.Signal=RCC_OSC32_IN
PC15-OSC32_OUT.Mode=LSE-External-Oscillator
PC15-OSC32_OUT.Signal=RCC_OSC32_OUT
PF0-OSC_IN.Mode=HSE-External-Oscillator
PF0-OSC_IN.Signal=RCC_OSC_IN
PF1-OSC_OUT.Mode=HSE-External-Oscillator
PF1-OSC_OUT.Signal=RCC_OSC_OUT
board=custom

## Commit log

2019-08-16 First bus board draft
2019-09-27 Bus layout
2019-09-27 Bus schema + layout (cont.)
2019-09-29 Bus progress
2019-09-29 Synth Bus Board finished
    This version was just sent to JLCPCB as rev 0.
2019-10-30 Simulation of output level shifters
2019-10-31 Add pulse to osc simulation
2019-11-03 Initial work on oscillator module
2020-01-16 Continued work on OSC1
2020-01-19 Documentation and verifying hard+soft sync
2020-03-29 Revert "PWM"
    This reverts commit d376f1211e99f4c40a807b6edc23770ccc192675.
    This is to solve a merge conflict. The changes in "PWM" will applied
    again.
2020-03-29 Locked all pots and jacks
2020-04-02 PWM input (same config as d376f1211e99)
2020-04-02 osc1: plan component placement
2020-04-03 osc1: all but 6 traces routed (crudely)
2020-04-04 osc1: routed +12V, -12V and +5V
2020-04-05 osc1: all nets routed, drc pass
2020-04-14 osc1: all but hole diameters in frontplate done
2020-04-14 osc1: extracted frontplate to a new project
2020-04-14 osc1: add frontplate silkscreen design (Affinity)
2020-04-14 osc1: gerbers for osc1 frontplate rev 0
2020-04-14 osc1: gerbers for osc1 rev 0
2020-05-16 osc1: rev 0 fixes
    Many minor fixes. Biggest change is adding a -5V LDO regulator.
2020-05-23 Add 3D model of Thonkiconn
2020-05-23 Add vertical pot 3D model
2020-05-23 Add final fixes for rev 1
    - 3D models for many parts
    - Hysteresis between PWM and PULSOUT for better pulse shape (see datasheet)
    - Fix a few resistor values that were unknown
    - Layout of -5V regulator
    - And more ...
2020-10-10 OSC1 rev 1 production files
2020-10-11 Changes after opening OSC1 with KiCAD 5.1.7
2020-10-17 Move content of jomag/don-midi to this repo
2020-10-17 midi: rename midi-to-cv to just midi
2020-10-20 State immediately after running cargo generate
2020-10-20 Basic, working project, with openocd and gdb configured and running
2022-12-17 Uncommitted MIDI changes
2022-12-25 Minor changes in PCB
2023-01-04 MIDI2CV rev 0
2023-01-04 Kicad 6 project files, new 3d models, etc
2023-05-16 Midi2CV component selection partly done
2023-05-16 Saved with new version of KiCAD
2023-05-16 midi2cv: completed bom selection and migrated to newer version of kicad
2023-10-22 midi: first prototype populated
